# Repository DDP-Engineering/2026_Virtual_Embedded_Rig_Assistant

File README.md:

# VERA — Virtual Embedded Rig Assistant

**A desktop agent workbench for electronics and embedded engineering.**

VERA is a desktop application in the style of Claude Code, Codex and opencode, organised around a
virtual workbench: a local folder that holds a project's documents, skills and tools. You chat with
a model; the agent searches the documents, reads and edits workbench files with your approval, and
saves session artifacts.

**Status:** the VERA 1.0 plan (milestones M0–M5) is implemented; later work is planned in
[00_Planning](00_Planning/README.md).

**Setup** (Windows or Ubuntu, needs Python 3.11+ and Git): `python 02_Tools/environment/setup.py` installs the
pinned Node.js and the npm packages inside the repository. Details: [02_Tools](02_Tools/README.md).

| Folder | Content |
|---|---|
| [00_Planning](00_Planning/README.md) | architecture, decisions and the implementation plan |
| [01_Documentation](01_Documentation/README.md) | project-wide documentation |
| [02_Tools](02_Tools/README.md) | environment, build and release tooling; the local toolchain |
| [03_Hardware](03_Hardware/README.md) | hardware profiles and bench setups |
| [04_HardwareDocu](04_HardwareDocu/README.md) | datasheets and hardware references |
| [05_Software](05_Software/README.md) | VERA source, functional tests and evaluators |
| [06_SoftwareDocu](06_SoftwareDocu/README.md) | software documentation |
| [07_Delivery](07_Delivery/README.md) | packages and release notes |
| [09_Others](09_Others/README.md) | supporting material |

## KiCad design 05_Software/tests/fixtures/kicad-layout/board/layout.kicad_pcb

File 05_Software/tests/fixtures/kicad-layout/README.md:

# kicad-layout fixtures

Input data of `tests/integration/kicad-layout.test.ts`. Everything here is fictional.

## board/

`make_fixtures.py` writes `board/layout.kicad_pcb` (KiCad 10 format, deterministic UUIDs derived from names) with
the writers of `../kicad/make_fixtures.py`; `layout.kicad_pro`, `fp-lib-table` and `fixture.pretty/` are its
project and footprint library. Run `python make_fixtures.py` from this folder after changing it.

- Two copper layers (F.Cu, B.Cu), an Edge.Cuts rectangle from (100, 100) to (150, 130) mm, default rules (0.2 mm
  clearance, 0.25 mm tracks, 0.8/0.4 mm vias).
- A small regulator circuit: connector J1 (VIN, GND), regulator U1 (SOT-23: GND, VOUT, VIN), feedback divider R1/R2
  (VOUT, FB, GND), and a decoupling capacitor C1 (VIN, GND) placed far from U1 so that the tests can move it close
  and route it.
- R3 and R4 on net SENSE, unrouted, for `align`; a locked mounting hole H1 (a non-plated hole) for the locked-item
  refusals.
- Existing routes: VIN on F.Cu from J1 to U1 (0.5 mm), VOUT from U1 to R1, FB from R1 to R2, a locked GND track on
  B.Cu with a via and a GND track on F.Cu to R2, so that DRC, the unconnected count and the unchanged check have
  items to compare.

## hooks/

- `hook.py`: run inside the helper at named points (`KICAD_LAYOUT_TEST_HOOK`, `HOOK_POINT`, `HOOK_ACTION`): move an
  item the request did not name, sleep inside the commit (after the first operation) so that the test can stop the
  helper, or stop the PCB editor (a lost connection).
- `editor_stub.py`: a PCB editor that never serves the API (`KICAD_LAYOUT_TEST_EDITOR`).
- `nudge.py`: a second API client (`uv run --script`): unsaved moves, revert, whether an API answers, and the open
  documents with the in-memory text's SHA-256.

VERA never passes these test variables to plugin programs: its runner gives a program only an allowlisted
environment.

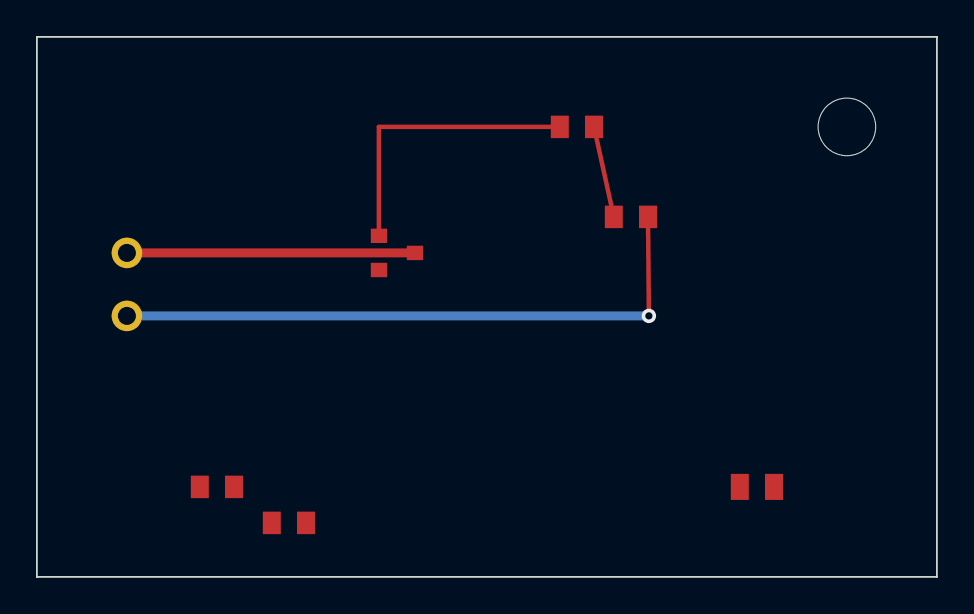
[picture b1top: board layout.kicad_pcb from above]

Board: 2 copper layers, 50.0 x 30.0 mm, 8 parts (0 on the bottom side), 5 nets.

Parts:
C1: 100n; C_0805
H1: MountingHole; MountingHole_3.2mm
J1: PWR_IN; Conn_2_THT
R1, R2: 10k; R_0805
R3, R4: 1k; R_0805
U1: REG; SOT-23

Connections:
FB: R1.2, R2.1
GND: C1.2, J1.2, R2.2, U1.1
SENSE: R3.1, R4.1
VIN: C1.1, J1.1, U1.3
VOUT: R1.1, U1.2

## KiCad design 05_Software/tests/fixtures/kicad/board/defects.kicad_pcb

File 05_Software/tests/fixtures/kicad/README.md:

# kicad fixtures

Fictional KiCad 10 projects for `tests/integration/kicad.test.ts`, written by `make_fixtures.py` (run it from
this folder with any Python 3.10+; UUIDs derive from names, so the output is deterministic). Every expected
value below follows from the design the script draws, and was written down before the helper existed; KiCad
10.0.8 confirmed each one. None was copied from `kicad-tool` output. Part numbers (`FX-...`) and circuits are
fictional.

Each project carries its own symbol library `fixture.kicad_sym` and footprint library `fixture.pretty`, named by
`sym-lib-table` / `fp-lib-table` with `${KIPRJMOD}` paths, so KiCad needs no global library.

`internals.py` reaches states no command line can arrange: the KiCad the helper finds (`locate`), the search
order of KiCad discovery over fake roots (`discover`), a missing or non-10 kicad-cli (`version`), a kicad-cli
that fails, writes nothing, cannot start, leaves a truncated Gerber or no job file (`fail`), a project file
that resolves outside its folder (`linkout`), a lower parse limit (`limit`), a source file changed during a
kicad-cli call (`change`), a call held long enough to stop the process tree (`slow`), every kicad-cli argument list recorded
(`calls`), and the document fitter fed oversized documents (`fit`).

## hier - hierarchy, instances, nets and BOM

Sheets (name path, file):

| Path | File | Page |
|---|---|---|
| `/` | `hier.kicad_sch` | 1 |
| `/ch1/` | `channel.kicad_sch` | 2 |
| `/ch2/` | `channel.kicad_sch` | 3 |
| `/monitor/` | `sub/monitor.kicad_sch` | 4 |
| `/monitor/probe/` | `sub/probe.kicad_sch` | 5 |

`sub/monitor.kicad_sch` names its sheet file `probe.kicad_sch`: KiCad resolves a sheet file from the folder of
the schematic that contains the sheet, so it is `sub/probe.kicad_sch`.

Root: J1 `PWR_IN` (pin 1 +5V, pin 2 GND), U1 `LDO_3V3` (IN +5V, OUT +3V3, GND), C1 10uF on +5V, C2, C3 and C10
10uF on +3V3 (C3 do-not-populate), H1 `MountingHole` (excluded from the BOM, no pins), J2 `EN_IN` (pin 1 EN_A,
pin 2 EN_B), PWR_FLAGs on +5V and GND. Each `channel` instance: R1 1k from EN to LED, D1 `LED_G` from LED
(anode, pin 2) to GND (cathode, pin 1), R2 100k from EN to GND; annotated R101/D101/R102 in ch1 and
R201/D201/R202 in ch2. `monitor`: R401 and R402 10k from +3V3 through MID to GND; `probe`: TP501 on MID.

Instances: 17 (8 root, 3 per channel, 2 monitor, 1 probe); power symbols and flags are not instances. The
channel symbols appear twice with the same symbol UUID and different sheet UUID paths: identity is the sheet
path plus the symbol UUID, never the reference.

Nets (8): `+3V3` {U1.2, C2.1, C3.1, C10.1, R401.1}; `+5V` {J1.1, U1.3, C1.1}; `GND` {J1.2, U1.1, C1.2, C2.2,
C3.2, C10.2, D101.1, D201.1, R102.2, R202.2, R402.2}; `/EN_A` {J2.1, R101.1, R102.1}; `/EN_B` {J2.2, R201.1,
R202.1}; `/ch1/LED` {R101.2, D101.2}; `/ch2/LED` {R201.2, D201.2}; `/monitor/MID` {R401.2, R402.1, TP501.1}. The
EN nets carry the root labels' names because KiCad names a net after the label of the highest sheet; the LED
net exists once per channel instance.

BOM (`Quantity,References,Value,Footprint,MPN,DNP`, rows ordered by their first reference):

| Qty | References | Value | Footprint | MPN | DNP |
|---|---|---|---|---|---|
| 3 | C1,C2,C10 | 10uF | fixture:C_0805 | FX-C0805-10U | |
| 1 | C3 | 10uF | fixture:C_0805 | FX-C0805-10U | yes |
| 2 | D101,D201 | LED_G | fixture:LED_0603 | FX-LED-G | |
| 1 | J1 | PWR_IN | fixture:Conn_2_THT | | |
| 1 | J2 | EN_IN | fixture:Conn_2_THT | | |
| 2 | R101,R201 | 1k | fixture:R_0603 | FX-R0603-1K | |
| 2 | R102,R202 | 100k | fixture:R_0603 | FX-R0603-100K | |
| 2 | R401,R402 | 10k | fixture:R_0603 | FX-R0603-10K | |
| 1 | TP501 | TP | fixture:TestPoint | | |
| 1 | U1 | LDO_3V3 | fixture:SOT-23 | FX-LDO33 | |

C10 follows C2 (natural order); the DNP C3 is a row of its own; H1 is in `excluded`. 16 instances in rows.
ERC: no violation (every pin is connected, +5V and GND carry a PWR_FLAG, +3V3 is driven by U1's output).
Power nets for the review (a `power_in` or `power_out` pin): `+3V3`, `+5V`, `GND`.

## erc - planted ERC defects

Root: two 10k resistors from BUS to GND, both annotated R1 (a duplicate reference), a GND PWR_FLAG, U1 `LOAD` with a power input on +12V that nothing drives,
a 10.16 mm wire at (127, 76.2) that touches nothing, and two instances `blk1`, `blk2` of `block.kicad_sch`,
whose buffer U (U101 / U201) has an unconnected input and drives BUS from its output.

| Sheet | Type | Severity | Object |
|---|---|---|---|
| `/` | `power_pin_not_driven` | error | the +12V power symbol's input pin (#PWR105) |
| `/` | `wire_dangling` | error | the wire |
| `/` | `unconnected_wire_endpoint` | warning | the wire (one per free end, 2) |
| `/blk1/` | `pin_not_connected` | error | U101 pin 1 |
| `/blk1/` | `pin_not_driven` | error | U101 pin 1 |
| `/blk2/` | `pin_not_driven` | error | U201 pin 1 |
| `/blk1/` | `pin_to_pin` | error | U101 pin 2 and U201 pin 2 (two outputs on BUS) |

8 violations: 6 errors, 2 warnings. KiCad marks an unconnected pin once per sheet file (on its first instance)
but checks drivers per instance, and reports a conflict once per net. KiCad 10.0.8's ERC does not report the
duplicate R1; kicad-tool's own check lists it under `duplicateReferences`: R1, unit 1, 2 instances, both on `/`.
Power symbols (references starting with `#`) are not counted: two GND power symbols on the root share
`#PWR101` on purpose, and KiCad's counts stay 6/2.

kicad-tool reads files from KiCad 8 on (schematic format 20231120, board 20240108); the tests refuse a copy saved
in KiCad 7's format. An instance entry with an empty reference is unannotated: KiCad 10.0.8's netlist shows it as
`R?`, so it is no duplicate.

## board - layout facts, DRC defects and exports

`defects.kicad_pcb`, 2 copper layers, outline 50 x 30 mm from (100, 100) to (150, 130), board thickness 1.6 mm,
stackup F.Mask 0.01, F.Cu 0.035, core 1.51 FR4 (er 4.5, tan d 0.02), B.Cu 0.035, B.Mask 0.01.

| Footprint | Position | Pads |
|---|---|---|
| J1 Conn_2_THT | (105, 110) | 1 VIN, 2 GND at (105, 113.5); drill 1.0 |
| R1 R_0805 | (115, 110) | 1 VIN (114.05), 2 OUT (115.95) |
| R2 R_0805 | (125, 110) | 1 OUT, 2 GND |
| R3 R_0805 | (115, 120) | 1 GND, 2 SIG |
| R4 R_0805 | (121, 105) | 1 SIG, 2 SPARE |
| H1 MountingHole_3.2mm | (145, 125) | NPTH 3.2, excluded from position files and BOM |

Tracks: VIN 1 segment 9.05 mm (0.5 wide); OUT 1 segment 8.1 mm; GND 2 segments, 20.95 mm on B.Cu and 3.5 mm on
F.Cu, 24.45 mm; SIG 2 segments, 4.1 + 15 = 19.1 mm. One GND via 0.8/0.4 at (125.95, 113.5). One GND zone on
B.Cu. Net classes (`defects.kicad_pro`): Default (clearance 0.2, track 0.25, via 0.8/0.4) and Power (clearance
1.0, track 0.5), pattern `VIN` -> Power.

DRC (2 violations, 1 unconnected item):
- `tracks_crossing` (error): the SIG track (120.05, 120)-(120.05, 105) crosses the OUT track on F.Cu at y = 110.
- `clearance` (error): R1 pad 1 (VIN, Power class 1.0 mm) to pad 2 (OUT): gap 1.9 - 1.0 = 0.9 mm < 1.0 mm.
- unconnected: R3 pad 1 (GND) has no track; KiCad pairs it with the nearest GND copper, the B.Cu track.

The same counts hold after `--refill-zones` (the zone is on B.Cu, away from the defects).

Exports: Gerbers for F.Cu, B.Cu, F.Mask, B.Mask, Edge.Cuts give 5 files with `%TF.FileFunction` (Copper L1 Top,
Copper L2 Bot, Soldermask Top/Bot, Profile) and the job file. Drill: PTH 3 holes (via 0.4 x 1, J1 1.0 x 2),
NPTH 1 hole (3.2). Position file: 5 rows (J1, R1, R2, R3, R4; H1 excluded). Board statistics: 6 footprints,
pads 2 through-hole, 8 SMD, 1 NPTH, 1 through via.

`clean.kicad_pcb`: R1 alone on a 20 x 10 mm board, nets A and B on one pad each: no violation, nothing
unconnected.

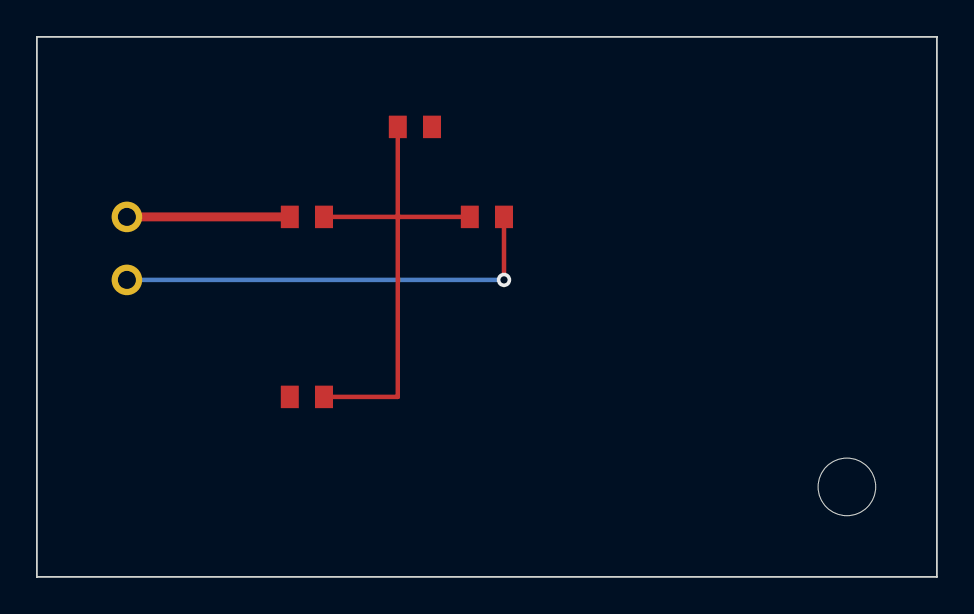
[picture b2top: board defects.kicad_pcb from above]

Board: 2 copper layers, 50.0 x 30.0 mm, 6 parts (0 on the bottom side), 4 nets.

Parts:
H1: MountingHole; MountingHole_3.2mm
J1: PWR_IN; Conn_2_THT
R1, R2: 1k; R_0805
R3, R4: 10k; R_0805

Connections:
GND: J1.2, R2.2, R3.1
OUT: R1.2, R2.1
SIG: R3.2, R4.1
VIN: J1.1, R1.1
